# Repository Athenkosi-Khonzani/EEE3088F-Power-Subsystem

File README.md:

# 🐭 Micro-Mouse Power Module  
### Power System for a Maze-Solving Robot

## 📌 Project Overview  
This project involves the design, development, and testing of a power module for a simplified micro-mouse robot. The micro-mouse is a small autonomous robot designed to navigate and solve a maze. While the processor, motherboard, and sensing modules are pre-designed, this project focuses exclusively on the power subsystem—an essential component responsible for delivering stable and reliable energy to all parts of the robot.

---

## ⚙️ Features  
- 🔋 **Battery Charging Circuitry** – Safely charges a lithium-ion battery using onboard circuitry (USB-C interface with USB hosting).  
- ⚡ **Power Distribution** – Provides regulated power to motors, sensors, processor, and other modules.  
- 🚗 **Motor Power Handling** – Supports high-current outputs required for driving motors.  
- 🧷 **Load Switches** – Supports additional switches to be used when required to drive high power loads.  
- 🔌 **USB-C Power Input** – Supports external USB-C charging and system powering.  
- 📉 **State-of-Charge (SOC) Monitoring** – Monitors battery voltage levels for feedback and safety. 

---

## 📦 What's Included  
- ✅ Circuit schematic (KiCad)  
- ✅ PCB layout  
- ✅ Bill of Materials (BOM)  
- ✅ Testing and validation documentation  
- ✅ I2C SOC readout
- ✅ SOC measurement logic

---

## ✅ Scope  
- Hardware design and testing of the power module  
- Battery management, charging, and safety  
- Power routing to all micro-mouse modules  
- ON/OFF logic and SOC measurement circuitry

---

## ❌ Not Included  
- Maze-solving algorithm and navigation logic  
- Mechanical assembly or robot chassis design  
- Sensor signal processing and interpretation  
- Processor firmware (Will be dealt with in design 2)

---

## 🛠️ Tools Used  
- 🖥️ KiCad
- 🔌 JLCPCB tools

## 👥 Contributors  
- **Athenkosi Khonzani [KHNATH002], Olwethu Khanzi [KHNOLW003]** – Power Module Design & Implementation  
- **Group 19**  

---

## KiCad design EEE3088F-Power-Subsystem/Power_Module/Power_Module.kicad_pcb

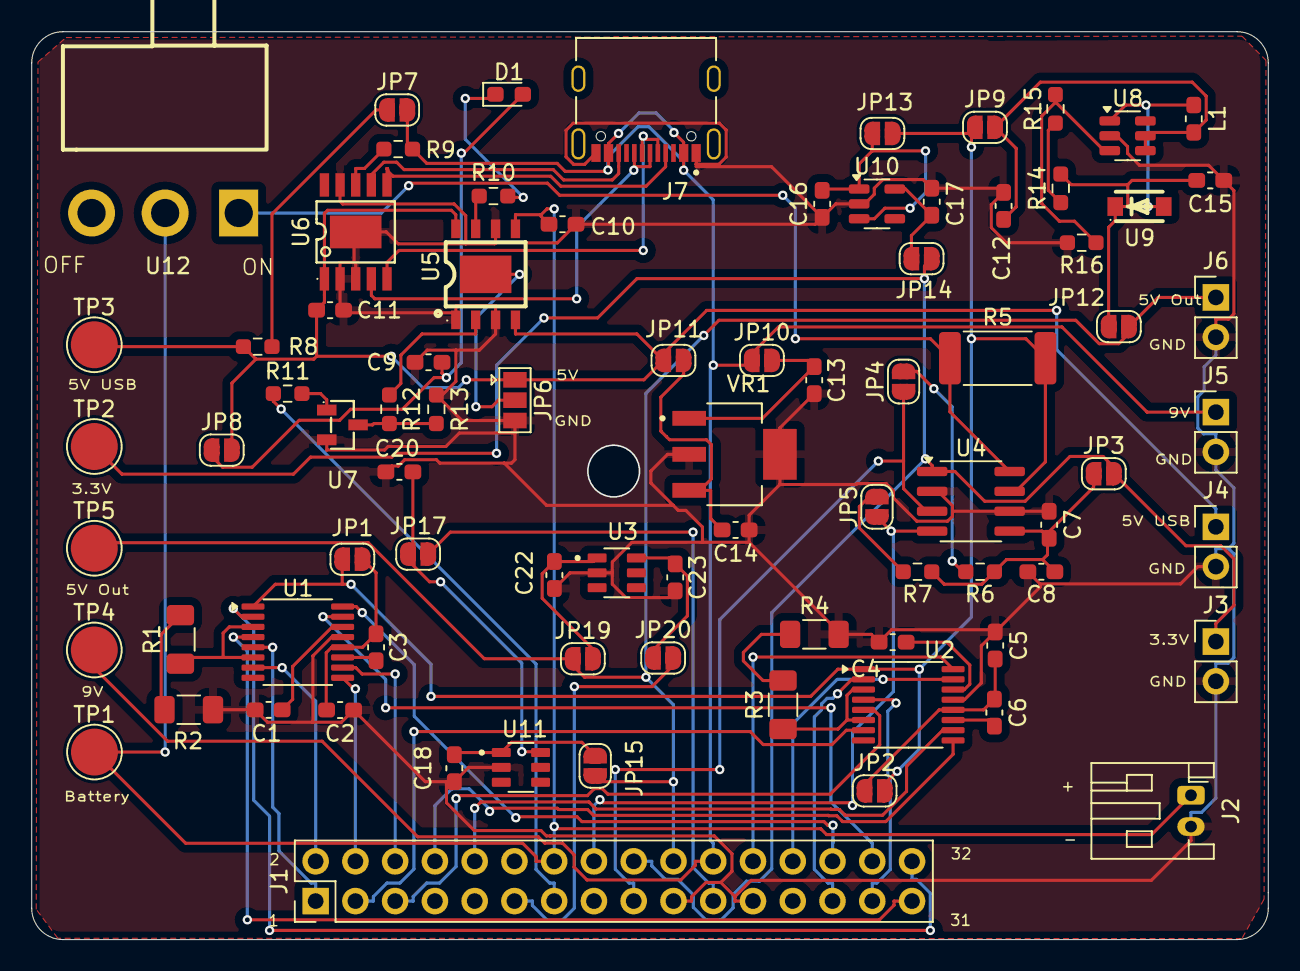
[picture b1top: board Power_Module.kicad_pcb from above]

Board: 2 copper layers, 79.0 x 58.0 mm, 82 parts (0 on the bottom side), 68 nets.

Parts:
C1, C4: 2.2u; C_0603_1608Metric_Pad1.08x0.95mm_HandSolder
C2, C5, C7, C9, C10: 10u; C_0603_1608Metric_Pad1.08x0.95mm_HandSolder
C3, C6: 10n; C_0603_1608Metric_Pad1.08x0.95mm_HandSolder
C8, C14: 0.1u; C_0603_1608Metric_Pad1.08x0.95mm_HandSolder
C11, C16, C17, C18, C22: 1u; C_0603_1608Metric_Pad1.08x0.95mm_HandSolder
C12, C15, C20, C23: 22u; C_0603_1608Metric_Pad1.08x0.95mm_HandSolder
C13: 0.22u; C_0603_1608Metric_Pad1.08x0.95mm_HandSolder
D1: LED; LED_0603_1608Metric_Pad1.05x0.95mm_HandSolder
J1: Conn_02x16_Odd_Even; PinHeader_2x16_P2.54mm_Vertical
J2: Conn_01x02_Pin; JST_PH_S2B-PH-K_1x02_P2.00mm_Horizontal
J3, J4, J5, J6: Conn_01x02_Pin; PinHeader_1x02_P2.54mm_Vertical
J7: TYPE-C-31-M-12; HRO_TYPE-C-31-M-12
JP1: +M1_in; SolderJumper-2_P1.3mm_Open_RoundedPad1.0x1.5mm
JP2: +M2_in; SolderJumper-2_P1.3mm_Open_RoundedPad1.0x1.5mm
JP3: +3.3v_in; SolderJumper-2_P1.3mm_Open_RoundedPad1.0x1.5mm
JP4: pp_1; SolderJumper-2_P1.3mm_Open_RoundedPad1.0x1.5mm
JP5: pp_2; SolderJumper-2_P1.3mm_Open_RoundedPad1.0x1.5mm
JP6: EP; SolderJumper-3_P1.3mm_Open_Pad1.0x1.5mm
JP7: +9_main; SolderJumper-2_P1.3mm_Open_RoundedPad1.0x1.5mm
JP8: +5_ch; SolderJumper-2_P1.3mm_Open_RoundedPad1.0x1.5mm
JP9: +3.7_b; SolderJumper-2_P1.3mm_Open_RoundedPad1.0x1.5mm
JP10: +9V_in; SolderJumper-2_P1.3mm_Open_RoundedPad1.0x1.5mm
JP11: +5v_l; SolderJumper-2_P1.3mm_Open_RoundedPad1.0x1.5mm
JP12: +5_out; SolderJumper-2_P1.3mm_Open_RoundedPad1.0x1.5mm
JP13: +3.7_l; SolderJumper-2_P1.3mm_Open_RoundedPad1.0x1.5mm
JP14: +3.3_l2; SolderJumper-2_P1.3mm_Open_RoundedPad1.0x1.5mm
JP15: sip_in_1; SolderJumper-2_P1.3mm_Open_RoundedPad1.0x1.5mm
JP17: sip_out_1; SolderJumper-2_P1.3mm_Open_RoundedPad1.0x1.5mm
JP19: sip_in_2; SolderJumper-2_P1.3mm_Open_RoundedPad1.0x1.5mm
JP20: sip_out_2; SolderJumper-2_P1.3mm_Open_RoundedPad1.0x1.5mm
L1: 10u; L_0603_1608Metric_Pad1.05x0.95mm_HandSolder
R1, R2, R3, R4: 100m; R_1206_3216Metric_Pad1.30x1.75mm_HandSolder
R5: 2m; R_2512_6332Metric_Pad1.40x3.35mm_HandSolder
R6, R7: 4.7k; R_0603_1608Metric_Pad0.98x0.95mm_HandSolder
R8, R10, R11: 1k; R_0603_1608Metric_Pad0.98x0.95mm_HandSolder
R9, R15: 10k; R_0603_1608Metric_Pad0.98x0.95mm_HandSolder
R12: 2k; R_0603_1608Metric_Pad0.98x0.95mm_HandSolder
R13: 3k; R_0603_1608Metric_Pad0.98x0.95mm_HandSolder
R14: 100k; R_0603_1608Metric_Pad0.98x0.95mm_HandSolder
R16: 15k; R_0603_1608Metric_Pad0.98x0.95mm_HandSolder
TP1: +Batt; TestPoint_Pad_D3.0mm
TP2: +3.3V; TestPoint_Pad_D3.0mm
TP3: +5V; TestPoint_Pad_D3.0mm
TP4: +9V_usb; TestPoint_Pad_D3.0mm
TP5: 5V_out; TestPoint_Pad_D3.0mm
U1, U2: DRV8833PW; TSSOP-16_4.4x5mm_P0.65mm
U3, U11: TPS22810DBVR; SOT95P280X145-6N
U4: INA219AxD; SOIC-8_3.9x4.9mm_P1.27mm
U5: TP4056; ESOP-8_L4.9-W3.9-P1.27-LS6.0-BL-EP
U6: CH224K; ESSOP-10_L4.9-W3.9-P1.0-LS6.0-TL-EP
U7: MMBT5551_C2145; SOT-23-3_L2.9-W1.3-P1.90-LS2.4-BR
U8: MT3608; SOT-23-6
U9: SM4007PL; SOD-123F_L2.8-W1.8-LS3.7-RD
U10: AP2112K-3.3; SOT-23-5
U12: SS-12D06L5; SW-TH_3P-P4.70_L11.1-W12.7
VR1: LM7805MPX_NOPB; VREG_LM7805MPX_NOPB

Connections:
5V_out: J1.20, J6.1, JP12.2 (B), JP15.1 (A), JP19.1 (A), TP5.1
+3.3V: J1.18, J3.1, JP3.2 (B), JP14.2 (B), TP2.1, U4.1 (A1)
+5V: C11.1, J4.1, JP6.1 (A), JP8.2 (B), JP11.2 (B), R8.2, TP3.1, U5.4 (VCC), U5.8 (CE), U6.1 (VDD)
+9V: J1.22, J5.1, J7.A4_B9 (VBUS), J7.B4_A9 (VBUS), JP7.2 (B), JP10.1 (A), R9.1, TP4.1
+BATT: C10.1, J1.14, J2.1, TP1.1, U5.5 (BAT), U12.2
/Motor_Drivers/VCP1: C3.2, U1.11 (VCP)
/Motor_Drivers/VCP2: C6.2, U2.11 (VCP)
/Usb_Charging/CHRG: R10.2, U5.7 (CHRG#)
/Usb_Charging/DM: J7.A7 (DN1), J7.B7 (DN2), U6.5 (DM)
/Usb_Charging/DP: J7.A6 (DP1), J7.B6 (DP2), U6.4 (DP)
/Usb_Charging/RPROG: R12.1, U5.2 (PROG)
FAST_CHRG_CTRL: J1.13, R11.1
GND: C1.1, C2.2, C4.1, C5.2, C7.2, C8.2, C9.2, C10.2, C11.2, C12.2, C13.2, C14.2, C15.2, C16.2, C17.2, C18.2, C20.2, C22.2, C23.2, J1.19, J1.23, J2.2, J3.2, J4.2, J5.2, J6.2, J7.A1_B12 (GND), J7.B1_A12 (GND), JP6.3 (B), R2.2, R4.2, R13.2, R16.2, U1.13 (GND), U2.13 (GND), U3.2 (GND), U4.2 (A0), U4.6 (GND), U5.1 (TEMP), U5.3 (GND), U5.6 (STDBY#), U6.2 (CFG2), U6.3 (CFG3), U6.9 (CFG1), U6.11 (GND), U7.2 (E), U8.2 (GND), U10.2 (GND), U11.2 (GND), VR1.2 (GND_2), VR1.4 (GND_4)
LOAD: JP1.2 (B), JP2.2 (B), JP9.1 (A), JP13.1 (A), R5.2, U1.1 (~SLEEP), U2.1 (~SLEEP), U4.7 (IN-)
LOUT1: J1.21, JP17.2 (B)
LOUT2: J1.11, JP20.2 (B)
M1_A_IN: J1.28, U1.16 (AIN1)
M1_A_OUT: J1.32, U1.2 (AOUT1)
M1_B_IN: J1.30, U1.15 (AIN2)
M1_B_OUT: J1.31, U1.4 (AOUT2)
M2_A_IN: J1.4, U1.9 (BIN1)
M2_A_OUT: J1.2, U1.7 (BOUT1)
M2_B_IN: J1.6, U1.10 (BIN2)
M2_B_OUT: J1.1, U1.5 (BOUT2)
M3_A_IN: J1.24, U2.16 (AIN1)
M3_A_OUT: J1.27, U2.2 (AOUT1)
M3_B_IN: J1.26, U2.15 (AIN2)
M3_B_OUT: J1.29, U2.4 (AOUT2)
M4_A_IN: J1.8, U2.9 (BIN1)
M4_A_OUT: J1.3, U2.7 (BOUT1)
M4_B_IN: J1.10, U2.10 (BIN2)
M4_B_OUT: J1.5, U2.5 (BOUT2)
unnamed: C9.1, D1.2 (A), JP8.1 (A)
unnamed: D1.1 (K), R10.1
unnamed: J7.A5 (CC1), U6.6 (CC2)
unnamed: J7.B5 (CC2), U6.7 (CC1)
unnamed: C2.1, C3.1, JP1.1 (A), U1.12 (VM)
unnamed: C5.1, C6.1, JP2.1 (A), U2.12 (VM)
unnamed: C7.1, C8.1, JP3.1 (A), R6.1, R7.1, U4.5 (VS)
unnamed: JP4.2 (B), R6.2
unnamed: JP5.2 (B), R7.2
unnamed: JP6.2 (C), U5.9 (EP)
unnamed: JP7.1 (A), R8.1
unnamed: C12.1, JP9.2 (B), L1.1, U8.4 (EN), U8.5 (IN)
unnamed: C13.1, JP10.2 (B), VR1.1 (INPUT)
unnamed: C14.1, JP11.1 (A), VR1.3 (OUTPUT)
unnamed: C15.1, JP12.1 (A), R14.1, U9.1 (C)
unnamed: C16.1, JP13.2 (B), U10.1 (VIN), U10.3 (EN)
unnamed: C17.1, JP14.1 (A), U10.5 (VOUT)
unnamed: C18.1, JP15.2 (B), U11.1 (VIN)
unnamed: C20.1, JP17.1 (A), U11.6 (VOUT)
unnamed: C22.1, JP19.2 (B), U3.1 (VIN)
unnamed: C23.1, JP20.1 (A), U3.6 (VOUT)
unnamed: R1.2, R2.1
unnamed: R3.2, R4.1
unnamed: R14.2, R15.1
unnamed: R1.1, U1.3 (AISEN), U1.6 (BISEN)
unnamed: C1.2, U1.14 (VINT)
unnamed: R3.1, U2.3 (AISEN), U2.6 (BISEN)
unnamed: C4.2, U2.14 (VINT)
unnamed: R5.1, U4.8 (IN+), U12.1
unnamed: R9.2, U6.8 (VBUS)
unnamed: R11.2, U7.1 (B)
unnamed: R12.2, R13.1, U7.3 (C)
unnamed: R15.2, R16.1, U8.3 (FB)
unnamed: L1.2, U8.1 (SW), U9.2 (A)
SCL: J1.16, JP5.1 (A), U4.4 (SCL)
SDA: J1.17, JP4.1 (A), U4.3 (SDA)

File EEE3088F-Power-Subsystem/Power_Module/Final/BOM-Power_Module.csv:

Comment,Designator,Footprint,LCSC,Quantity
10u,L1,L_0603_1608Metric_Pad1.05x0.95mm_HandSolder,C1035,1
INA219AxD,U4,SOIC-8_3.9x4.9mm_P1.27mm,C138706,1
0.1u,"C14,C8",C_0603_1608Metric_Pad1.08x0.95mm_HandSolder,C14663,2
1u,"C11,C16,C17,C18,C22",C_0603_1608Metric_Pad1.08x0.95mm_HandSolder,C15849,5
TP4056,U5,ESOP-8_L4.9-W3.9-P1.27-LS6.0-BL-EP,C16581,1
TYPE-C-31-M-12,J7,HRO_TYPE-C-31-M-12,C165948,1
MT3608,U8,SOT-23-6,C19189893,1
10u,"C10,C2,C5,C7,C9",C_0603_1608Metric_Pad1.08x0.95mm_HandSolder,C19702,5
TPS22810DBVR,"U11,U3",SOT95P280X145-6N,C205990,2
0.22u,C13,C_0603_1608Metric_Pad1.08x0.95mm_HandSolder,C21120,1
1k,"R10,R11,R8",R_0603_1608Metric_Pad0.98x0.95mm_HandSolder,C21190,3
MMBT5551_C2145,U7,SOT-23-3_L2.9-W1.3-P1.90-LS2.4-BR,C2145,1
15k,R16,R_0603_1608Metric_Pad0.98x0.95mm_HandSolder,C22809,1
LED,D1,LED_0603_1608Metric_Pad1.05x0.95mm_HandSolder,C2286,1
2k,R12,R_0603_1608Metric_Pad0.98x0.95mm_HandSolder,C22975,1
4.7k,"R6,R7",R_0603_1608Metric_Pad0.98x0.95mm_HandSolder,C23162,2
AP2112K-3.3,U10,SOT-23-5,C23380830,1
2.2u,"C1,C4",C_0603_1608Metric_Pad1.08x0.95mm_HandSolder,C23630,2
100m,"R1,R2,R3,R4",R_1206_3216Metric_Pad1.30x1.75mm_HandSolder,C25334,4
100k,R14,R_0603_1608Metric_Pad0.98x0.95mm_HandSolder,C25803,1
10k,"R15,R9",R_0603_1608Metric_Pad0.98x0.95mm_HandSolder,C25804,2
LM7805MPX_NOPB,VR1,VREG_LM7805MPX_NOPB,C2848241,1
2m,R5,R_2512_6332Metric_Pad1.40x3.35mm_HandSolder,C2994640,1
SS-12D06L5,U12,SW-TH_3P-P4.70_L11.1-W12.7,C319015,1
3k,R13,R_0603_1608Metric_Pad0.98x0.95mm_HandSolder,C4211,1
DRV8833PW,"U1,U2",TSSOP-16_4.4x5mm_P0.65mm,C50506,2
10n,"C3,C6",C_0603_1608Metric_Pad1.08x0.95mm_HandSolder,C57112,2
22u,"C12,C15,C20,C23",C_0603_1608Metric_Pad1.08x0.95mm_HandSolder,C59461,4
SM4007PL,U9,SOD-123F_L2.8-W1.8-LS3.7-RD,C64898,1
CH224K,U6,ESSOP-10_L4.9-W3.9-P1.0-LS6.0-TL-EP,C970725,1

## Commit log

2025-03-23 Modified README.md file
2025-03-23 First commit empty
2025-03-23 Basic structure in place; Need to put regulators
2025-03-23 Regulators in place - Protection circuitry neeeded
2025-03-23 Add main switch - still need to put in the right place
2025-03-23 All changes saved
2025-03-25 Added the main connector; fixed the labels; We need a switch
2025-03-25 Fixed minor but fundamental error
2025-03-25 Footprints added for all equipment; we still need to add protection circuitry
2025-03-25 fixed diode error
2025-03-26 Connectors and jumpers added. But there's still errors for some reason
2025-03-26 INA219 improved
2025-03-26 jlcpcb tools installed
2025-03-27 BASIC LAYOUT PUT: BAZIC LAYOUT PUT
2025-03-27 Alot has happened honestly
2025-03-28 Started pcb layout, still looking good
2025-03-28 Last commit, messy though
2025-04-21 Last commit
